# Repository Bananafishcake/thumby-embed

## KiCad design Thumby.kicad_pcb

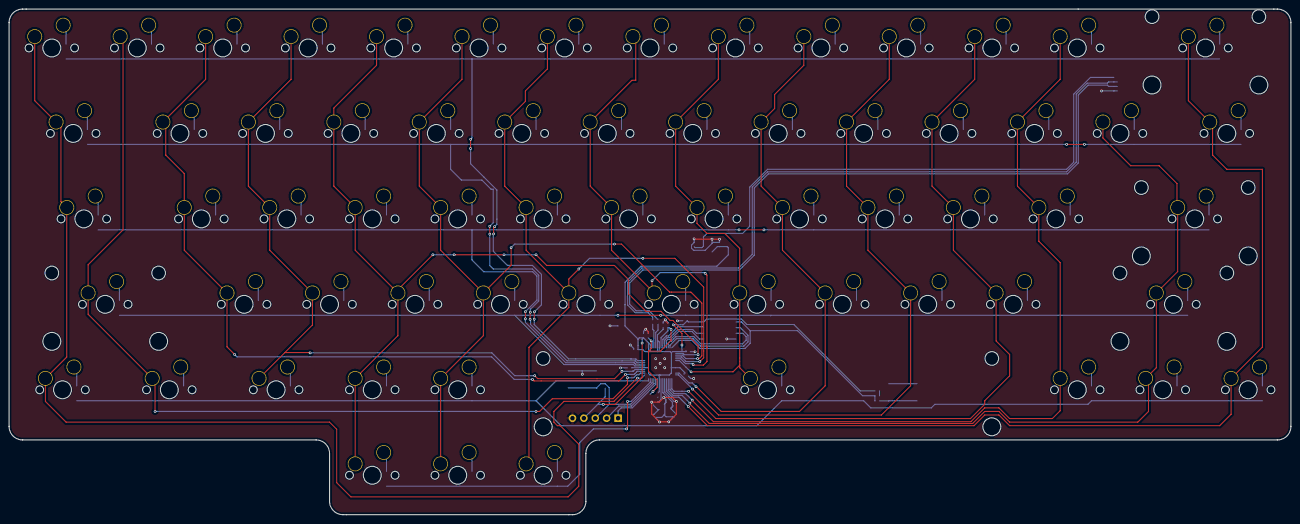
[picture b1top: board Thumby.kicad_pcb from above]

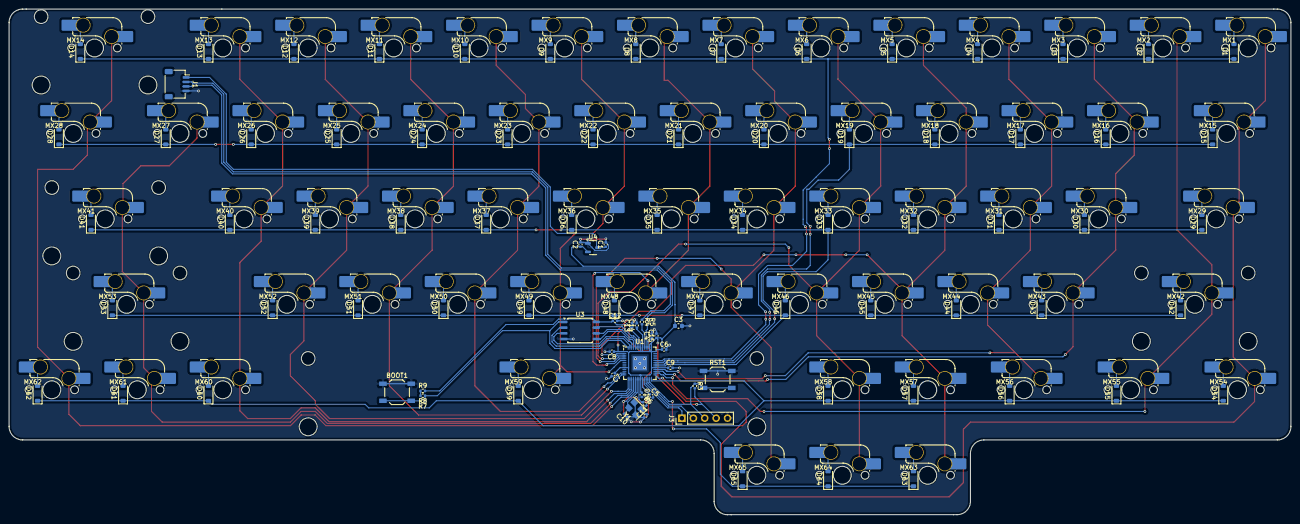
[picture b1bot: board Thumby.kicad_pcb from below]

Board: 2 copper layers, 285.8 x 112.7 mm, 161 parts (161 on the bottom side), 108 nets.

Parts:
BOOT1: SW_Push; SW_SPST_TL3342
C1, C2, C4, C6, C12: 1u; C_0402_1005Metric
C3: 10u; C_0603_1608Metric
C5, C7, C8, C9, C13, C14, C15, C16: 100n; C_0402_1005Metric
C10, C11: 22p; C_0402_1005Metric
D1, D2, D3, D4, D5, D6, D7, D8, D9, D10, D11, D12, D13, D14, D15, D16, D17, D18, D19, D20, D21, D22, D23, D24, D25, D26, D27, D28, D29, D30, D31, D32, D33, D34, D35, D36, D37, D38, D39, D40, D41, D42, D43, D44, D45, D46, D47, D48, D49, D50, D51, D52, D53, D54, D55, D56, D57, D58, D59, D60, D61, D62, D63, D64, D65: D_Small; D_SOD-123
J1: JST SH 4-PIN; JST_SH_SM04B-SRSS-TB_1x04-1MP_P1.00mm_Horizontal
J3: Conn_01x05; PinHeader_1x05_P2.54mm_Vertical
MX1, MX2, MX3, MX4, MX5, MX6, MX7, MX8, MX9, MX10, MX11, MX12, MX13, MX14, MX16, MX17, MX18, MX19, MX20, MX21, MX22, MX23, MX24, MX25, MX26, MX27, MX30, MX31, MX32, MX33, MX34, MX35, MX36, MX37, MX38, MX39, MX40, MX41, MX42, MX43, MX44, MX45, MX46, MX47, MX48, MX49, MX50, MX51, MX52, MX53, MX57, MX58, MX59, MX60, MX61, MX62, MX63, MX64, MX65: MX_SW_HS; SW_MX_HS_CPG151101S11_1u
MX15, MX28: MX_SW_HS; SW_MX_HS_CPG151101S11_1.5u
MX29: MX_SW_HS; SW_MX_HS_CPG151101S11_1.75u
MX54, MX55, MX56: MX_SW_HS; SW_MX_HS_CPG151101S11_1.25u
R3, R8, R9: 5.1K; R_0402_1005Metric
R4, R5: 27; R_0402_1005Metric
R6, R7: 1k; R_0402_1005Metric
RST1: SW_Push; SW_SPST_TL3342
U1: RP2040; QFN-56-1EP_7x7mm_P0.4mm_EP3.2x3.2mm
U3: W25Q128JVS; SOIC-8_5.23x5.23mm_P1.27mm
U4: XC6206PxxxMR; SOT-23-3
Y1: Crystal_GND24; Crystal_SMD_3225-4Pin_3.2x2.5mm

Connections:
+1V1: C4.1, C5.1, C13.1, U1.23 (DVDD), U1.45 (VREG_VOUT), U1.50 (DVDD)
+3V3: C2.1, C3.1, C6.1, C7.1, C8.1, C9.1, C12.1, C14.1, C15.1, C16.1, J3.4, R3.2, R9.2, U1.1 (IOVDD), U1.10 (IOVDD), U1.22 (IOVDD), U1.33 (IOVDD), U1.42 (IOVDD), U1.43 (ADC_AVDD), U1.44 (VREG_IN), U1.48 (USB_VDD), U1.49 (IOVDD), U3.8 (VCC), U4.2 (VO)
+5V: C1.1, J1.1, U4.3 (VI)
Col 0: MX1.1, MX15.1, MX29.1, MX54.1, U1.29 (GPIO18)
Col 1: MX2.1, MX42.1, MX55.1, U1.30 (GPIO19)
Col 2: MX3.1, MX16.1, MX30.1, MX43.1, U1.31 (GPIO20)
Col 3: MX4.1, MX17.1, MX31.1, MX44.1, MX56.1, U1.32 (GPIO21)
Col 4: MX5.1, MX18.1, MX32.1, MX45.1, MX57.1, MX63.1, U1.2 (GPIO0)
Col 5: MX6.1, MX19.1, MX33.1, MX46.1, MX58.1, MX64.1, U1.3 (GPIO1)
Col 6: MX7.1, MX20.1, MX34.1, MX47.1, MX65.1, U1.4 (GPIO2)
Col 7: MX8.1, MX21.1, MX35.1, MX48.1, U1.5 (GPIO3)
Col 8: MX9.1, MX22.1, MX36.1, MX49.1, MX59.1, U1.6 (GPIO4)
Col 9: MX10.1, MX23.1, MX37.1, MX50.1, U1.13 (GPIO10)
Col 10: MX11.1, MX24.1, MX38.1, MX51.1, U1.14 (GPIO11)
Col 11: MX12.1, MX25.1, MX39.1, MX52.1, U1.15 (GPIO12)
Col 12: MX13.1, MX26.1, MX40.1, MX60.1, U1.16 (GPIO13)
Col 13: MX27.1, MX41.1, MX53.1, MX61.1, U1.17 (GPIO14)
Col 14: MX14.1, MX28.1, MX62.1, U1.18 (GPIO15)
D+: J1.3, R4.1
D-: J1.2, R5.1
GND: BOOT1.1, C1.2, C2.2, C3.2, C4.2, C5.2, C6.2, C7.2, C8.2, C9.2, C10.1, C11.1, C12.2, C13.2, C14.2, C15.2, C16.2, J1.4, J3.5, RST1.1, U1.19 (TESTEN), U1.57 (GND), U3.4 (GND), U4.1 (GND), Y1.2, Y1.4
unnamed: BOOT1.2, R7.2
unnamed: C11.2, R6.2, Y1.1
unnamed: D1.2 (A), MX1.2
unnamed: D2.2 (A), MX2.2
unnamed: D3.2 (A), MX3.2
unnamed: D4.2 (A), MX4.2
unnamed: D5.2 (A), MX5.2
unnamed: D6.2 (A), MX6.2
unnamed: D7.2 (A), MX7.2
unnamed: D8.2 (A), MX8.2
unnamed: D9.2 (A), MX9.2
unnamed: D10.2 (A), MX10.2
unnamed: D11.2 (A), MX11.2
unnamed: D12.2 (A), MX12.2
unnamed: D13.2 (A), MX13.2
unnamed: D14.2 (A), MX14.2
unnamed: D15.2 (A), MX15.2
unnamed: D16.2 (A), MX16.2
unnamed: D17.2 (A), MX17.2
unnamed: D18.2 (A), MX18.2
unnamed: D19.2 (A), MX19.2
unnamed: D20.2 (A), MX20.2
unnamed: D21.2 (A), MX21.2
unnamed: D22.2 (A), MX22.2
unnamed: D23.2 (A), MX23.2
unnamed: D24.2 (A), MX24.2
unnamed: D25.2 (A), MX25.2
unnamed: D26.2 (A), MX26.2
unnamed: D27.2 (A), MX27.2
unnamed: D28.2 (A), MX28.2
unnamed: D29.2 (A), MX29.2
unnamed: D30.2 (A), MX30.2
unnamed: D31.2 (A), MX31.2
unnamed: D32.2 (A), MX32.2
unnamed: D33.2 (A), MX33.2
unnamed: D34.2 (A), MX34.2
unnamed: D35.2 (A), MX35.2
unnamed: D36.2 (A), MX36.2
unnamed: D37.2 (A), MX37.2
unnamed: D38.2 (A), MX38.2
unnamed: D39.2 (A), MX39.2
unnamed: D40.2 (A), MX40.2
unnamed: D41.2 (A), MX41.2
unnamed: D42.2 (A), MX42.2
unnamed: D43.2 (A), MX43.2
unnamed: D44.2 (A), MX44.2
unnamed: D45.2 (A), MX45.2
unnamed: D46.2 (A), MX46.2
unnamed: D47.2 (A), MX47.2
unnamed: D48.2 (A), MX48.2
unnamed: D49.2 (A), MX49.2
unnamed: D50.2 (A), MX50.2
unnamed: D51.2 (A), MX51.2
unnamed: D52.2 (A), MX52.2
unnamed: D53.2 (A), MX53.2
unnamed: D54.2 (A), MX54.2
unnamed: D55.2 (A), MX55.2
unnamed: D56.2 (A), MX56.2
unnamed: D57.2 (A), MX57.2
unnamed: D58.2 (A), MX58.2
unnamed: D59.2 (A), MX59.2
unnamed: D60.2 (A), MX60.2
unnamed: D61.2 (A), MX61.2
unnamed: D62.2 (A), MX62.2
unnamed: D63.2 (A), MX63.2
unnamed: D64.2 (A), MX64.2
unnamed: D65.2 (A), MX65.2
unnamed: R8.2, R9.1
unnamed: R5.2, U1.46 (USB_DM)
unnamed: R4.2, U1.47 (USB_DP)
Q_100: U1.53 (QSPI_SD0), U3.5 (DI(IO0))
Q_101: U1.55 (QSPI_SD1), U3.2 (DO(IO1))
Q_102: U1.54 (QSPI_SD2), U3.3 (IO2)
Q_103: U1.51 (QSPI_SD3), U3.7 (IO3)
Q_CLK: U1.52 (QSPI_SCLK), U3.6 (CLK)
Q_SEL: R7.1, R8.1, U1.56 (QSPI_SS), U3.1 (~CS)
RESET: J3.3, R3.1, RST1.2, U1.26 (RUN)
Row 0: D1.1 (K), D2.1 (K), D3.1 (K), D4.1 (K), D5.1 (K), D6.1 (K), D7.1 (K), D8.1 (K), D9.1 (K), D10.1 (K), D11.1 (K), D12.1 (K), D13.1 (K), D14.1 (K), U1.37 (GPIO25)
Row 1: D15.1 (K), D16.1 (K), D17.1 (K), D18.1 (K), D19.1 (K), D20.1 (K), D21.1 (K), D22.1 (K), D23.1 (K), D24.1 (K), D25.1 (K), D26.1 (K), D27.1 (K), D28.1 (K), U1.36 (GPIO24)
Row 2: D29.1 (K), D30.1 (K), D31.1 (K), D32.1 (K), D33.1 (K), D34.1 (K), D35.1 (K), D36.1 (K), D37.1 (K), D38.1 (K), D39.1 (K), D40.1 (K), D41.1 (K), U1.35 (GPIO23)
Row 3: D42.1 (K), D43.1 (K), D44.1 (K), D45.1 (K), D46.1 (K), D47.1 (K), D48.1 (K), D49.1 (K), D50.1 (K), D51.1 (K), D52.1 (K), D53.1 (K), U1.34 (GPIO22)
Row 4: D54.1 (K), D55.1 (K), D56.1 (K), D57.1 (K), D58.1 (K), D59.1 (K), D60.1 (K), D61.1 (K), D62.1 (K), U1.28 (GPIO17)
Row 5: D63.1 (K), D64.1 (K), D65.1 (K), U1.27 (GPIO16)
SWC: J3.1, U1.24 (SWCLK)
SWD: J3.2, U1.25 (SWD)
XIN: C10.2, U1.20 (XIN), Y1.3
XOUT: R6.1, U1.21 (XOUT)
